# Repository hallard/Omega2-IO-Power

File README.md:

Power FTDI SPI and I2C or Full GPIO Shields for Onion Omega2
============================================================

These shields are used to power and to expose [Onion Omega2](https://onion.io/) gpio pins. it has just few minimal features such as wiring and 3V3 regulator and exists in 2 versions

- **Basic**: same size than Omega2, exposing Serial/SPI/I2C 
- **Full**: little bigger but exposing all Omega2 pins

**Features**   

- I2C Pullups placement
- I2C 4 pins connector
- SPI 6 pins connector
- Full Omega2 GPIO pins (Full version only)
- FTDI connector to Omega2 Serial0 (SMD or PTH) 
- USB Mini connector to power the whole thing and Omega2

You can find more information on Omega2 on their [site](https://onion.io/), it's really well [documented](https://docs.onion.io/omega2-docs/index.html) here.

**Waiting for V1.0 Boards from [PCBs.io](https://PCBs.io). I did not fully tested them yet, I will update ASAP. Use at your own risks**

Detailed Description
====================

Very simple, you plug your Omega2 on the shield, then you're ready to go. But pay attention, this board run at 3.3V.

You have 2 options to power board :

- Mini USB connector 5V goes to 3V3 regulator and you're ready to go
- Close JP1 and use **Only 3V3** FTDI connector that already have regulator on board. FTDI connector will then power the shield and Omega2 without any Mini USB plugged.

Take care if you are powered with mini USB and you want to use FTDI cable to connect to console, use a 3V3 FTDI cable and do not close JP1 connector

Here are example of FTDI 3V3 connector that should work 

- SparkFun Beefy 3 [FTDI Basic Breakout](https://www.sparkfun.com/products/13746) up to 600mA out at 3V3
- RocketScream [USB/Serial with CH340](http://www.rocketscream.com/blog/product/ch340g-usb-serial-adapter/) up to 100mA out at 3V3
- EZSBC [Usb To Serial UART 5V or 3V3](https://www.tindie.com/products/ddebeer/usb-to-serial--uart-5v-or-33v-695-/) up to 250mA out at 3V3
- WeMos [CH340G Breakout 5V 3.3V USB to serial](https://www.aliexpress.com/store/product/WEMOS-CH340G-Breakout-5V-3-3V-USB-to-serial-module/1331105_32664922086.html) up to 300mA out at 3V3

Schematics
==========

**Basic version** Click on image to zoom   

**Full GPIO version** Click on image to zoom   

Boards
====== 

**Basic** Click on image to zoom   
&nbsp;&nbsp;&nbsp;

**Full GPIO version** Click on image to zoom   
&nbsp;&nbsp;&nbsp;

You can order PCB of [Basic Version](https://PCBs.io/share/4976j) or [Full GPIO Version](https://PCBs.io/share/4KEo9) at PCBs.io. PCBs.io give me reward when you order my designed boards from their site. This is pretty good, because I can use these rewards to create and design new boards and order boards for a discounted price and share new boards. So if you don't care about PCB manufacturer please use PCBs.io.

Assembled boards (V1.0)
=======================

**Basic**

**Full GPIO version**  

License
=======

This work is licensed under a Creative Commons Attribution-NonCommercial 4.0 International [License](http://creativecommons.org/licenses/by-nc/4.0)

If you want to do commercial stuff with this project, please contact [CH2i company](https://ch2i.eu) so we can organize an simple agreement.

Misc
====
See news and other projects on my [blog](https://hallard.me)

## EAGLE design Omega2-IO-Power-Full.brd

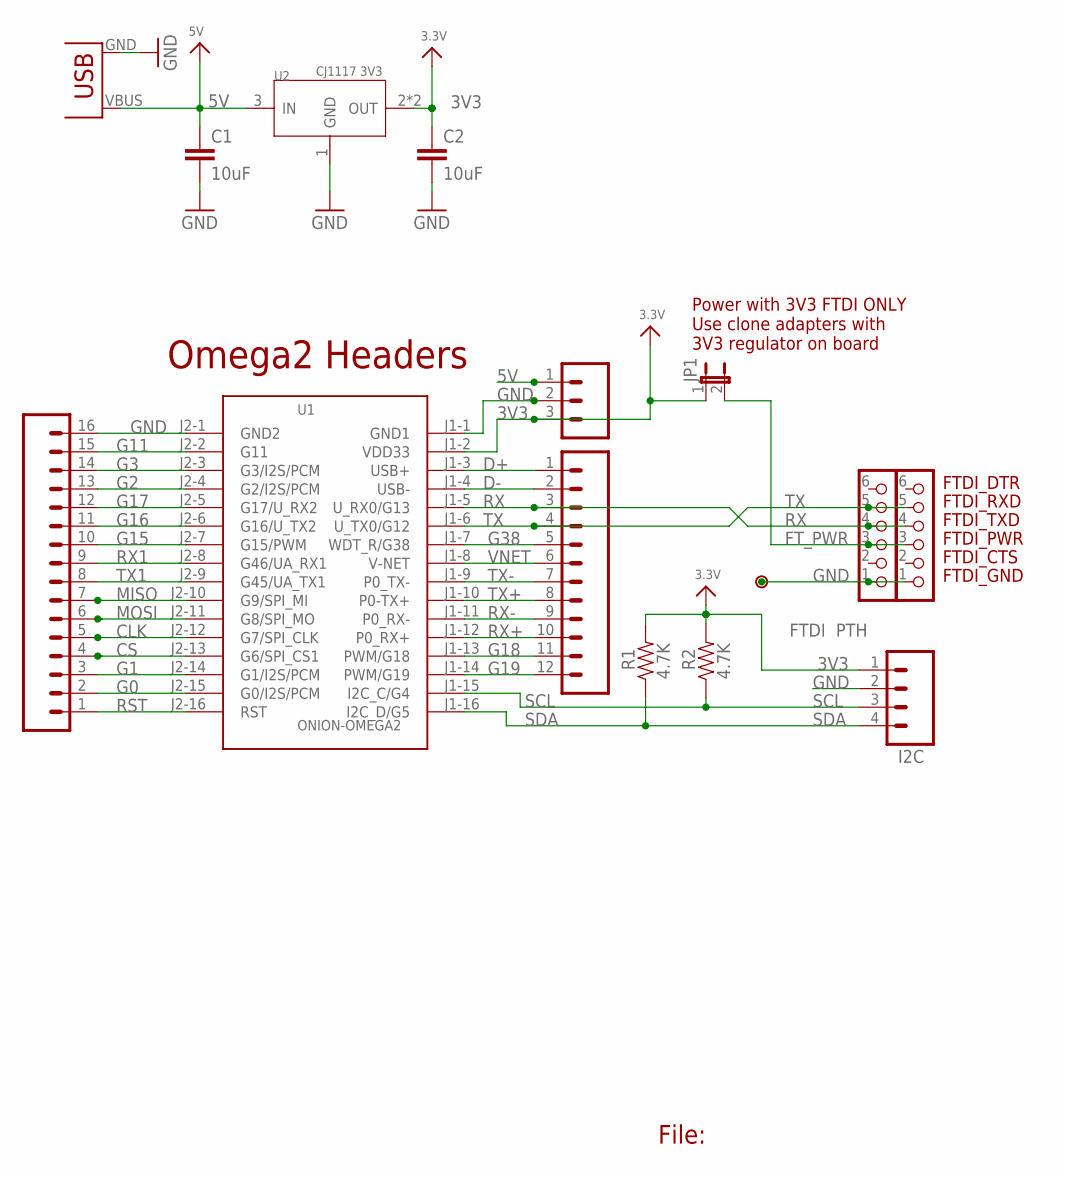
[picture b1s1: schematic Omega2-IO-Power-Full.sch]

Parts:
C1, C2: 10uF; 0805-CAP-LARGEPADS
FTDI: CON_HEADER_1X06-PTH; M1X6
I2C: M04PTH; 1X04
J1: M16PTH; 1X16
J2: M12PTH; 1X12
J7: M03PTH; 1X03
JP1: JUMPER2
P2: PADNORMAL; PAD
PTH: CON_HEADER_1X06; M1X6_MALE_RIGHT_ANGLED_SMD_NO_HOLES
R1, R2: 4.7K; 0805-RES
U1: ONION-OMEGA2; ONION-2MM-2X16
U2: CJ1117 3V3; SOT89
USB: USB_POWER; USB_MINIB_POWER

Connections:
3V3: C2.1, I2C.1, J7.3, JP1.1, R1.2, R2.2, U1.J1-2 (VDD33), U2.2 (OUT), U2.4 (OUT)
5V: C1.1, J7.1, U2.3 (IN), USB.VBUS (VCC)
CLK: J1.5, U1.J2-12 (G7/SPI_CLK)
CS: J1.4, U1.J2-13 (G6/SPI_CS1)
D+: J2.1, U1.J1-3 (USB+)
D-: J2.2, U1.J1-4 (USB-)
FT_PWR: FTDI.3, JP1.2, PTH.3
G0: J1.2, U1.J2-15 (G0/I2S/PCM)
G1: J1.3, U1.J2-14 (G1/I2S/PCM)
G2: J1.13, U1.J2-4 (G2/I2S/PCM)
G3: J1.14, U1.J2-3 (G3/I2S/PCM)
G11: J1.15, U1.J2-2 (G11)
G15: J1.10, U1.J2-7 (G15/PWM)
G16: J1.11, U1.J2-6 (G16/U_TX2)
G17: J1.12, U1.J2-5 (G17/U_RX2)
G18: J2.11, U1.J1-13 (PWM/G18)
G19: J2.12, U1.J1-14 (PWM/G19)
G38: J2.5, U1.J1-7 (WDT_R/G38)
GND: C1.2, C2.2, FTDI.1, I2C.2, J1.16, J7.2, P2.1, PTH.1, U1.J1-1 (GND1), U1.J2-1 (GND2), U2.1 (GND), USB.GND
MISO: J1.7, U1.J2-10 (G9/SPI_MI)
MOSI: J1.6, U1.J2-11 (G8/SPI_MO)
RST: J1.1, U1.J2-16 (RST)
RX: FTDI.4, J2.3, PTH.4, U1.J1-5 (U_RX0/G13)
RX1: J1.9, U1.J2-8 (G46/UA_RX1)
RX+: J2.10, U1.J1-12 (P0_RX+)
RX-: J2.9, U1.J1-11 (P0_RX-)
SCL: I2C.3, R2.1, U1.J1-15 (I2C_C/G4)
SDA: I2C.4, R1.1, U1.J1-16 (I2C_D/G5)
TX: FTDI.5, J2.4, PTH.5, U1.J1-6 (U_TX0/G12)
TX1: J1.8, U1.J2-9 (G45/UA_TX1)
TX+: J2.8, U1.J1-10 (P0-TX+)
TX-: J2.7, U1.J1-9 (P0_TX-)
VNET: J2.6, U1.J1-8 (V-NET)

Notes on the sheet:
File:
Omega2 Headers
FTDI_RXD
FTDI_TXD
FTDI_CTS
FTDI_DTR
FTDI_PWR
FTDI_GND
Power with 3V3 FTDI ONLY Use clone adapters with 3V3 regulator on board

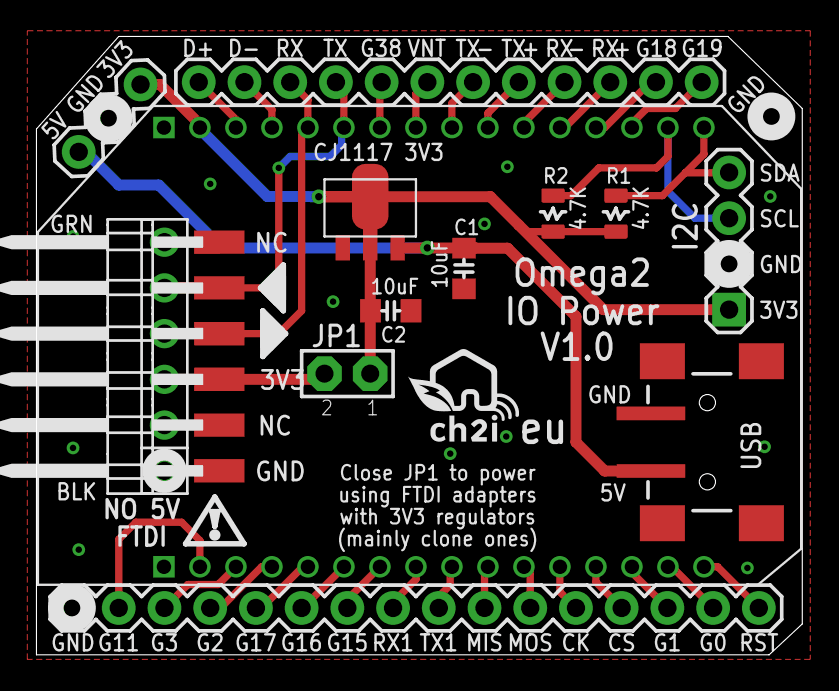
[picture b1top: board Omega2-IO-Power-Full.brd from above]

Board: 2 copper layers, 42.5 x 34.4 mm, 17 parts (1 on the bottom side), 33 nets.

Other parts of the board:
U$2: LOGO_C2I_015
U$3: LOGO_CH2I_110MM

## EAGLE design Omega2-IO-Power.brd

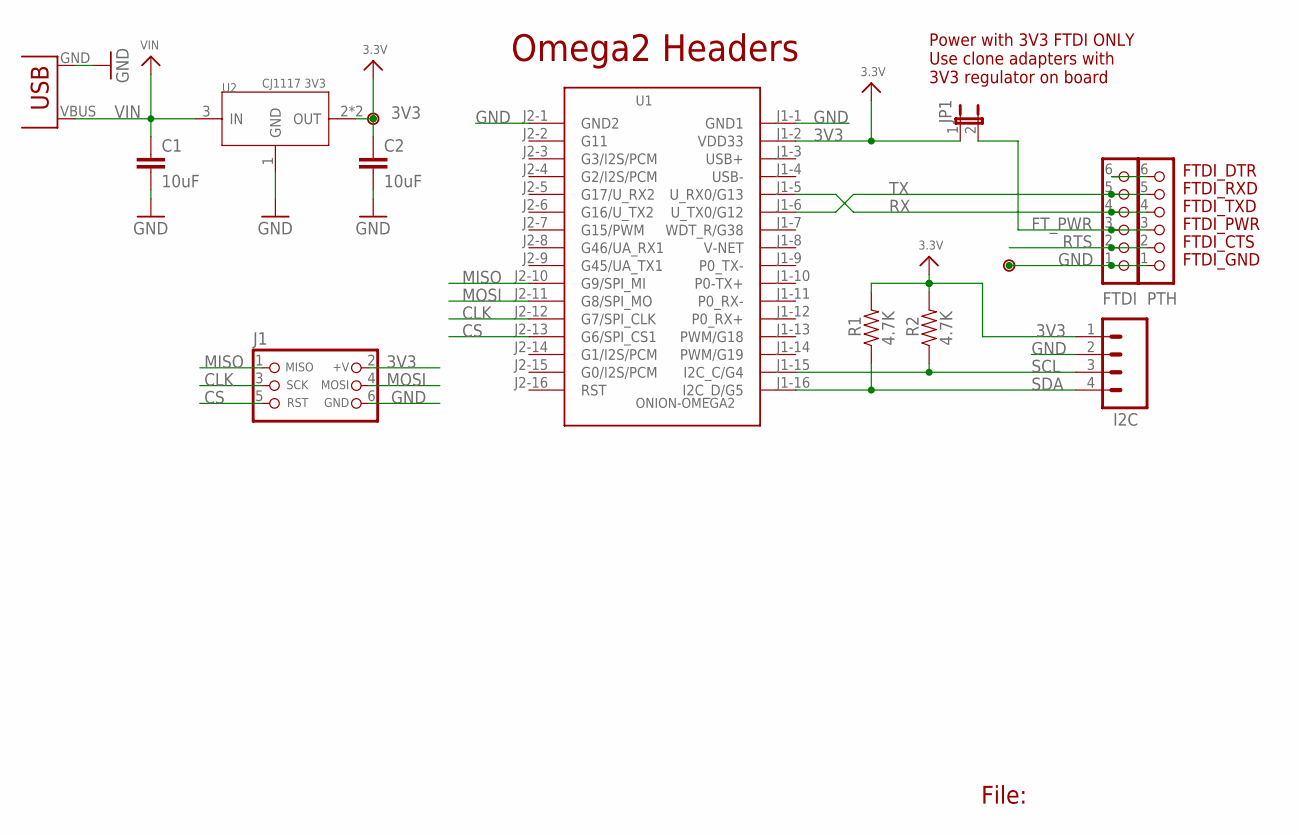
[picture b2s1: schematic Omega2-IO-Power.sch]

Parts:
C1, C2: 10uF; 0805-CAP-LARGEPADS
FTDI: CON_HEADER_1X06-PTH; M1X6
I2C: M04PTH; 1X04
J1: CON_HEADER_PRG_AVR_ICSP-PTH; HEADER_PRG_2X03
JP1: JUMPER2
P1, P2: PADNORMAL; PAD
PTH: CON_HEADER_1X06; M1X6_MALE_RIGHT_ANGLED_SMD_NO_HOLES
R1, R2: 4.7K; 0805-RES
U1: ONION-OMEGA2; ONION-2MM-2X16
U2: CJ1117 3V3; SOT89
USB: USB_POWER; USB_MINIB_POWER

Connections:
3V3: C2.1, I2C.1, J1.2 (+V), JP1.1, P1.1, R1.2, R2.2, U1.J1-2 (VDD33), U2.2 (OUT), U2.4 (OUT)
CLK: J1.3 (SCK), U1.J2-12 (G7/SPI_CLK)
CS: J1.5 (RST), U1.J2-13 (G6/SPI_CS1)
FT_PWR: FTDI.3, JP1.2, PTH.3
GND: C1.2, C2.2, FTDI.1, I2C.2, J1.6 (GND), P2.1, PTH.1, U1.J1-1 (GND1), U1.J2-1 (GND2), U2.1 (GND), USB.GND
MISO: J1.1 (MISO), U1.J2-10 (G9/SPI_MI)
MOSI: J1.4 (MOSI), U1.J2-11 (G8/SPI_MO)
RST: FTDI.6, PTH.6
RTS: FTDI.2, PTH.2
RX: FTDI.4, PTH.4, U1.J1-5 (U_RX0/G13)
SCL: I2C.3, R2.1, U1.J1-15 (I2C_C/G4)
SDA: I2C.4, R1.1, U1.J1-16 (I2C_D/G5)
TX: FTDI.5, PTH.5, U1.J1-6 (U_TX0/G12)
VIN: C1.1, U2.3 (IN), USB.VBUS (VCC)

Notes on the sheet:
File:
Omega2 Headers
FTDI_RXD
FTDI_TXD
FTDI_CTS
FTDI_DTR
FTDI_PWR
FTDI_GND
Power with 3V3 FTDI ONLY Use clone adapters with 3V3 regulator on board

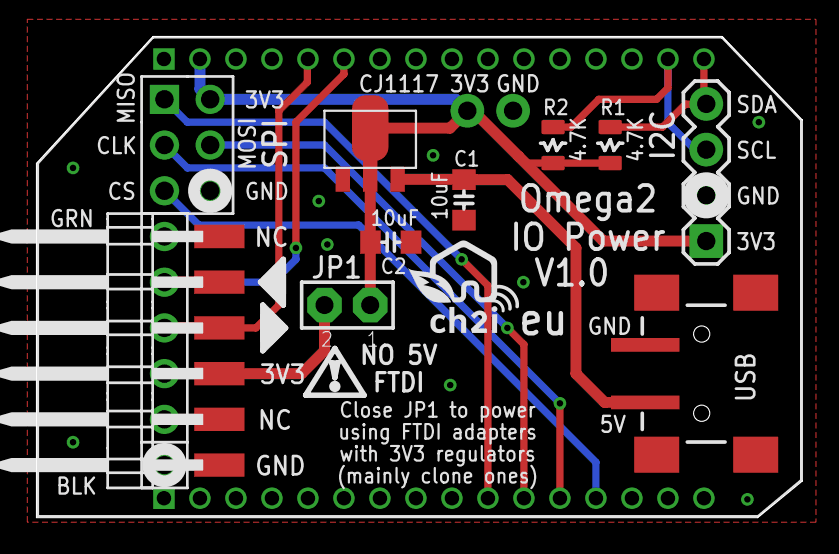
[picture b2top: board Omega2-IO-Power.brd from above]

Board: 2 copper layers, 42.5 x 26.7 mm, 16 parts (1 on the bottom side), 14 nets.

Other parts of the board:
U$2: LOGO_C2I_015
U$4: LOGO_CH2I_75MM

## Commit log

2017-01-17 :space_invader: Added .gitattributes
2017-01-17 Creation
2017-01-17 Added PCBs.io Link
2017-01-18 Pictures link fix
2017-01-18 cosmetic
2017-01-18 Fix Link
2017-01-18 deleted old reference
2017-01-18 Added Full version
2017-01-18 Image resize
2017-07-06 Added Assembled Pictures
2017-07-06 Picture Link
2017-07-06 link
2017-07-06 Added WEMOS CH340G
2017-07-06 added WeMos LDO features
2017-07-06 Added License Image

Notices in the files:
parts and their libraries:
microbuilder: This work is placed in the public domain, and may be freely used for commercial and non-commercial work with the following conditions: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
SparkFun-Connectors: Licensing: Creative Commons ShareAlike 4.0 International - https://creativecommons.org/licenses/by-sa/4.0
